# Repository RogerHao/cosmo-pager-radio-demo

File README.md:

# CosmoRadio

可穿梭于平行宇宙的 Radio 接收器

## 项目简介

桌面交互设备，安卓平板 + 3D 打印外壳 + ESP32 USB HID 控制器。造型参考 iMac G3 斜面站立式设计，用户通过旋钮调频、NFC 刷卡切换内容，仿佛在平行宇宙间搜索信号。

**当前版本：V4**（2026.04 — 2026.05）— 技术方案验证 + 单套原型制作

> 2026-04-29 与 Arthur 达成重启协议：第四期缩小为技术方案验证和单套原型制作，合同价 ¥5,000，目标 2026-05-20 左右交付。原 4 套整机 + 8 套电子套件交付范围已取消。

## 产品形态

- **外观风格**: iMac G3 斜面站立式，模块化三件式（主体 + 顶部 + 背板）
- **显示设计**: 三圆形遮罩（矩形屏幕通过开孔分割为三个圆形显示区）
- **输入方式**: 2 × EC11 旋钮 + Kailh 机械轴按钮 (6.25U 卫星轴) + NFC 刷卡
- **状态指示**: WS2812 RGB LED

## 硬件组成（V4）

| 组件 | 规格 | 用途 |
|------|------|------|
| 安卓平板 | 客户自购 (Samsung Galaxy Tab A9 8.7") | 主机，运行 Web 应用 |
| ESP32-S3 DevKitC N16R8 | 36+ GPIO / USB OTG / 16MB Flash / 8MB PSRAM | HID 控制器 |
| 定制 PCB 载板 | **100×100mm 双面** (JLCPCB 免费打样)，**两条 1×22 单排母** + 5 路 XH2.54 + 4× 10kΩ/10nF 去抖 | 消灭飞线，XH2.54 即插即用 |
| EC11 旋钮 × 2 | 15mm 半轴柄旋转编码器 | 频率调节 / 模式切换 |
| Kailh BOX 轴 + 6.25U 卫星轴 | 机械键盘蝴蝶结构，3.6mm 行程 | Action Button |
| RC522 mini NFC 模块 × 1 | 13.56MHz SPI，读 NTAG215 NDEF | NFC 刷卡交互（最终 1 个，2026-05-06 确认） |
| **OTG dongle (YK16-09E V1) 内置子板** | 拆 USB-A 母座，4 飞线接 J5 → DevKitC 排针 GPIO19/20 + 5V/GND | 平板 Data Host + Power Sink 同时工作 |
| 板载 RGB LED | DevKitC GPIO48 WS2812B | 状态指示（不外接 LED）|

## 连接方案

| 方案 | 固件位置 | 状态 |
|------|----------|------|
| USB HID | 项目根目录 | **当前使用** — TinyUSB，即插即用 |
| BLE HID | (已删除，见 git 历史) | V1-V2 遗留，已停用 |

## 交互设计

输入设备通过 ESP32 USB HID 协议作为标准键盘连接到安卓平板，事件以模拟按键传递：

| 输入 | 映射 | 功能 |
|------|------|------|
| 顶部 Action 按钮 | Enter 键 | 确认选择 |
| EC11 左 旋转 | 上/下方向键 | 调节频率 |
| EC11 左 按下 | F1（占位，平板可重映射） | 扩展功能位 |
| EC11 右 旋转 | 左/右方向键 | 切换模式 |
| EC11 右 按下 | F2（占位，平板可重映射） | 扩展功能位 |
| NFC 卡（写了 NDEF Text） | `<payload>\n` | **主路径**：固件读卡上写入的字符串，原样键入 + Enter（无前缀） |
| NFC 卡（空白 / 非 NDEF） | `NFC:<UID>\n` | 兜底：识别失败时键入 UID 方便诊断 |

### NFC 协议设计

为了让产品身份与 NFC 卡 UID 解耦（UID 不可控且需要逐张录入），固件读取卡上的 NDEF Text Record 内容作为产品 ID。流程：

1. 出厂前用任一手机 NFC 工具 app 把每张卡写入特定字符串（如 `R01`、`track-42`）
2. 用户放卡 → 固件读 NDEF → HID 键入 `R01\n`
3. 平板侧 Android 应用结合页面状态/输入长度判断当前是 NFC payload 还是普通 HID 键入；`NFC:` 前缀仅出现在 UID 兜底路径，方便区分

### LED 状态指示（DevKitC 板载 GPIO48 RGB LED）

| 事件 | LED 颜色 |
|------|----------|
| 按钮按下 | 红色 |
| 按钮释放 | 熄灭 |
| NFC 识别中（键入期间） | 蓝色 |
| 启动完成 | 绿色闪烁 |

## 项目结构

```
cosmo-radio/                            # 项目根 = ESP-IDF USB HID 固件
├── main/
│   ├── tusb_hid_example_main.c         # 入口：USB HID + ASCII→HID 编码
│   ├── input_handler.c/h               # GPIO 中断输入（按钮 + 双 EC11）
│   ├── nfc_handler.c/h                 # RC522 SPI 扫描 + NDEF Text 解析
│   └── led_indicator.c/h               # 板载 WS2812 RGB（GPIO48）
├── sdkconfig.defaults
├── CMakeLists.txt
├── pcb/                                # KiCad 工程 + JLCPCB 上板资料（待开始）
├── docs/
│   ├── assets/                         # 元器件引脚图、原型照片
│   ├── firmware/                       # 固件实现文档
│   ├── hardware/                       # 硬件模块设计方案（NFC、USB...）
│   ├── legacy/                         # 弃用内容
│   └── project/ → codex                # BOM、PCB Spec、项目主文档
└── test/
    └── hid-test.html
```

## 相关项目

- [cosmo-pager-web-nextjs-vercel](https://github.com/RogerHao/cosmo-pager-web-nextjs-vercel) — Web 应用前端（客户软件团队开发）

## 版本历史

| 版本 | 时间 | 主控 | 连接 | 主要变化 |
|------|------|------|------|----------|
| V1 | 2025 Q3-Q4 | Adafruit HUZZAH32 | — | 硬件预研 |
| V2 | 2025.12-2026.01 | XIAO ESP32S3 | BLE HID | 首批组装，硅谷交付 |
| V3 | 2026.01-2026.02 | ESP32-S3 SuperMini | USB HID | BLE→USB 切换，12 套交付 |
| **V4** | **2026.04-2026.05** | **ESP32-S3 DevKitC N16R8** | **USB HID** | **模块化 PCB + NFC + 机械按钮，单套原型验证** |

## V4 进度

**2026-05-07 整体技术方案验证完成 ✅**——电气、固件、NFC 协议端到端跑通。后续是 PCB 板设计 + 结构件设计。

电气与固件：
- [x] 原 12 套 BOM 定稿 + 报价（单套 ¥79，已取消）
- [x] 2026-04-29 与 Arthur 重启 V4：技术方案验证 + 单套原型，合同价 ¥5,000
- [x] USB-C 充电方案：被动 SS34 注入实测失败 → 改为内置一分二 OTG 线材小板（已采购验证）
- [x] NFC 数量确认：1 个 RC522 mini（2026-05-06）
- [x] 万能板飞线原型焊接 + GPIO 验证（2026-05-06，[图片](docs/assets/v4-handmade-prototype-2026-05-06.jpg)）
- [x] 固件 V4 GPIO 迁移（SuperMini → DevKitC N16R8）
- [x] NFC 驱动开发（RC522 SPI + NDEF Text Record 解析）
- [x] 旋钮 + NFC HID 协议定稿（`#<payload>\n` + UID 兜底）
- [x] 端到端验证：iPhone 写卡 → ESP32 读 NDEF → HID 键入 `#112358\n`（2026-05-07）

待办（V4 收尾）：
- [ ] PCB 载板设计（KiCad → JLCPCB），把万能板飞线版固化为正式板
- [ ] Arthur 寄新 Tab A9（原 Pad 已损坏）→ HID + 充电链路回归
- [ ] 按钮机构验证（6.25U 卫星轴空格键 + 3D 打印键帽）
- [ ] 外壳 3D 模型适配（Arthur Fusion 360）+ 打印装配
- [ ] 单套整机原型组装 + 整机测试
- [ ] 交付技术验证报告 + 单套原型

## 构建与烧录

```bash
get_idf                                    # 激活 ESP-IDF 环境
idf.py set-target esp32s3                  # 设置目标芯片（首次）
idf.py build                               # 构建
idf.py -p /dev/cu.usbmodem* flash monitor  # 烧录并监控
```

## GPIO 引脚分配（V4 终版）

> N16R8 = 8MB octal PSRAM，**GPIO 26-37 全段被内部 octal SPI flash + PSRAM 占用，不可使用**。完整表和"PCB 位置"列见 [CLAUDE.md](CLAUDE.md) "GPIO Pin Assignments"。

| 功能 | GPIO | 连接器 (PCB 位置) |
|------|------|--------|
| EC11-L (用户左旋钮) A/B/SW | **42 / 41 / 40** | J1 (PCB 左侧中段, 5P) |
| EC11-R (用户右旋钮) A/B/SW | **17 / 18 / 8** | J2 (PCB 右侧中段, 5P) |
| Action Button | 1 | J3 (PCB 左侧靠前, 2P) |
| RC522 NFC RST/IRQ/MISO/MOSI/SCK/CS | 4 / 5 / 6 / 7 / 15 / 16 | J4 (PCB 右侧, 8P, SPI2 via GPIO Matrix) |
| OTG USB D-/D+ | 19 / 20 | J5 (PCB 左侧靠后, 4P) → dongle USB |
| 板载 RGB LED | 48 | DevKitC 板载，无外接 LED |

> EC11 A/B 信号 PCB 上各加 10kΩ 上拉 + 10nF 对地 RC 去抖。
> V3 引脚分配（SuperMini）见 git 历史。

## 文档索引

- [V4 待办事项](TODO.md)
- [V4 BOM 及报价分析](docs/project/CosmoRadio-V4-BOM及报价分析.md)
- [V4 PCB 载板规格](docs/project/CosmoRadio-V4-PCB-Spec.md)
- [项目主文档](docs/project/cosmoradio-yangweile-customized-hardware.md)
- [USB 接口方案](docs/hardware/usb.md)
- [NFC 模块方案](docs/hardware/nfc.md)
- [OTG 一分二适配器（内置子板）](docs/hardware/otg-adapter.md)

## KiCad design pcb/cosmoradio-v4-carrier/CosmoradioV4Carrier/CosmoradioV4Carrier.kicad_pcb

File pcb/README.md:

# CosmoRadio V4 PCB

CosmoRadio V4 的 PCB 目标是做一块 ESP32-S3 DevKitC N16R8 载板，用于技术方案验证和单套原型制作。

当前阶段不追求量产最优，而是追求：

- 可快速打样
- 可手工装配
- 可稳定验证 USB HID、外部充电、旋钮、按钮、NFC
- 出问题时容易测量和返修

## 当前范围

| 项目 | 结论 |
|------|------|
| 合作状态 | 2026-04-29 与 Arthur 重启 V4 |
| 当前交付 | 技术方案验证 + 单套原型制作 |
| 合同价 | ¥5,000 |
| 目标时间 | 2026-05-20 左右 |
| 核心风险 | PCB 设计与验证 |
| 非当前目标 | 原 4 套整机 + 8 套电子件批量交付 |

## 2026-05-07 整体方案验证完成 ✅

| 项目 | 状态 |
|------|------|
| NFC 数量 | ✅ 确认 **1 个** RC522 mini |
| 一分二 OTG + 充电线材 | ✅ 已采购多种型号，测试出一种比较理想，作为内置子板基准 |
| 手工万能板原型 | ✅ 已焊出（[图片](../docs/assets/v4-handmade-prototype-2026-05-06.jpg)）：ESP32-S3 DevKitC + 拆解后的一分二小板 + 4 路 XH2.54 连接器 |
| 测试机 | ⚠️ 原 R4 Tab A9 已损坏，临时用安卓手机替代验证；新 Tab A9 到货后需回归 |
| 连接器布局 | 左上 J4 NFC 8P / 右上 J3 Action Button 2P / 左中 J1 EC11 左 5P / 右中 J2 EC11 右 5P |
| GPIO 分配 | ✅ V4 终版定稿（2026-05-06），详见 [CLAUDE.md](../CLAUDE.md) |
| 外接 LED | ❌ 不接（用 DevKitC 板载 GPIO48 RGB LED 做调试） |
| EC11 接线 | 3 IO + 共地（C 与 SW2 都接 GND，无需 VCC，靠 ESP32 内部上拉） |
| 固件 V4 GPIO 迁移 | ✅ 完成（2026-05-06）；V3 SuperMini pinout 完全弃用 |
| RC522 NFC 驱动 | ✅ 1MHz SPI，NDEF Text Record 解析跑通（2026-05-07） |
| HID 协议 | ✅ `#<payload>\n` 主路径 + `NFC:<UID>\n` 兜底（2026-05-07） |
| 端到端验证 | ✅ iPhone 写卡 "112358" → ESP32 读 NDEF → HID 键入 `#112358\n`（2026-05-07） |

**剩余工作集中在 PCB 设计 + 结构件**——所有方案级未知都已收敛。

## 下一阶段：PCB 落版（Plan v2，2026-05-18 锁定）

详细方案见 `~/.claude/plans/iridescent-snuggling-planet.md`。要点：

- 把万能板飞线版 1:1 复制到 KiCad（连接器位置、网络名都已经在飞线上验证过）
- ESP32-S3 DevKitC N16R8 用**两条 1×22 单排母**（不是 2×22 双排，单排好焊好对齐），间距 22.86mm
- **5 路 XH2.54 连接器**（J1 EC11-L / J2 EC11-R / J3 BTN / J4 NFC / J5 OTG USB 数据）
- OTG dongle (YK16-09E V1) 拆 USB-A 母座后 4 飞线焊到 J5 公头线
- **EC11 A/B 信号外加 10kΩ + 10nF RC 去抖**（4 R + 4 C，全 0805 贴片）—— 解决飞线版"一格不准"
- NFC SPI 时钟可尝试拉回 5MHz（铜箔走线 + 模块自带去耦应该够）
- 板尺寸 **100×100mm 双面板**（JLC 免费打样上限），无 USB-C 母座、无 SS34、无外接 LED

## 板子定位

这不是完整 ESP32 主控板，而是 **ESP32-S3 DevKitC N16R8 carrier board**。

ESP32-S3 DevKitC 通过 2.54mm 排母插在 PCB 上，PCB 只负责：

- 固定主控与外设线束
- 消灭 V3 的万能板和飞线
- 将旋钮、按钮、LED、NFC、USB-C 接口标准化
- 提供必要的上拉、电阻、二极管、去耦
- 支持单套原型的调试和返修

```mermaid
flowchart LR
    tablet[Android 平板] <-- USB HID --> pcb[CosmoRadio V4 PCB]
    charger[USB-C 充电器] --> pcb
    pcb --> devkit[ESP32-S3 DevKitC N16R8]
    pcb --> enc1[EC11 左旋钮]
    pcb --> enc2[EC11 右旋钮]
    pcb --> top[顶部按钮 / LED]
    pcb --> nfc[RC522 NFC 模块]
```

## 已确认事实

### 主控

- 使用 ESP32-S3 DevKitC N16R8，不再使用 V3 的 ESP32-S3 SuperMini。
- DevKitC 插在载板上，不直接焊死。
- ESP32-S3 原生 USB OTG 固定使用 GPIO19 / GPIO20。
- 当前固件仍是 V3/SuperMini pinout，后续必须迁移到 V4 pinout。

### 输入与输出

- 两个 EC11 旋钮，每个旋钮有 A / B / SW。
- Action Button 使用 Kailh BOX 轴 + 6.25U 卫星轴，本质是单路低电平按钮。
- LED 使用 WS2812B，数据线串 330R。
- NFC 使用 RC522 mini 模块，通过 SPI 连接，不把 MFRC522 芯片集成到主板。

### USB 与供电

- 平板是 Samsung Galaxy Tab A9 8.7"。
- 平板侧需要同时承担 USB Host 和充电需求。
- HID 必须走有线 USB；BLE HID 之前已经测试过，不稳定，排除出当前主路径。
- V3 已经通过 Type-C 一分二 OTG 线材验证：Tab A9/Android 手机可以同时接收 ESP32 USB HID 输入并充电。
- 当前问题不是“原理是否成立”，而是 V3 的一分二线材太长、外露、形态差。
- V4 目标是尽可能把一分二线材里的 OTG + 充电能力集成到 PCB/内部结构中，减少外露线材。
- 市面上容易买到的是 OTG + 充电转接线/小扩展坞，不是适合直接嵌入主 PCB 的裸模块。

```mermaid
flowchart LR
    tablet[Tab A9] <-- USB Host 数据 --> sub[内置一分二 OTG + 充电子系统]
    charger[USB-C 充电器] --> sub
    sub <-- USB HID --> esp[ESP32-S3 DevKitC]
    esp --> io[旋钮 / 按钮 / LED / NFC]
```

当前 USB/充电路径按三档处理：

| 档位 | 方案 | 当前定位 |
|------|------|----------|
| P0 | 外购一分二 OTG + 充电线材整件 | V3 已验证成立；继续作为功能基准 |
| P1 | 拆解一分二线材，取内部 PCB，短线/板内固定 | 当前最现实的 V4 原型方向 |
| P2 | 自研 LDR6028/LDR6023C OTG + 充电子板 | 可集成，但先作为后续方案，不塞进第一版主板风险内 |

被动 VBUS 注入方案已经降级为失败路径记录，不再作为主线：

- J6 充电输入 USB-C
- J5 平板输出 USB-C
- J6 VBUS 通过 SS34 注入 J5 VBUS
- J5 / J6 CC1 和 CC2 视转接板实测情况配置 5.1k Rd

原因：6P Type-C 转接板即使有 5.1k Rd，也只能让手机/平板识别到 OTG 设备；它不能让平板同时完成 Data Host 和 Power Sink 的角色组合。实测中，两个 6P 转接板直连、或通过 SS34 注入外部 5V，都无法让手机/平板进入充电状态。

不能把 CH224K、HUSB238 这类 PD Sink/诱骗芯片当成完整解法。它们主要解决“从充电器取电压”，不负责让平板同时保持数据 Host 和供电 Sink，也不负责完整 USB 数据/供电角色编排。

### USB/充电可选方案重审

问题本质：Tab A9 必须同时处于 **Data Host** 和 **Power Sink**。这不是普通 USB-C 默认角色，默认情况下 Host 往往也是供电 Source。要让平板一边 Host ESP32，一边被外部充电，需要角色拆分。

| 方案 | 是否能集成到主 PCB | 风险 | 结论 |
|------|-------------------|------|------|
| 拆解已验证一分二线材并内置小板 | 半集成 | 低中 | 第一版最现实，解决形态问题优先 |
| LDR6028 5V OTG + 充电子板 | 能 | 中 | 元件少，可后续小板验证；不一定比成品便宜 |
| LDR6023C 双口 charge-through 子板 | 能 | 中高 | 更接近成品线材内部方案，但外围更复杂 |
| 标准 USB-C PD charge-through | 能 | 高 | 正规方案，但不适合当前预算和周期 |
| 被动/半主动 SS34 注入 | 能 | 已实测失败 | 不再作为主线 |
| BLE HID + USB-C 只负责充电 | 能 | 低 | 已排除：BLE HID 实测不稳定，且当前要求必须有线 HID |

当前主路径：

1. 用已验证一分二线材作为功能基准。
2. 买 2-3 条同类线材拆解，优先寻找尺寸小、焊点清晰、可固定的内部 PCB。
3. 第一版 V4 主 PCB 给内置子板预留安装区、短线焊盘、测试点和应力释放。
4. 只有当成品线材内部 PCB 不适合内置，才启动 LDR6028/LDR6023C 自研小板。

标准 PD charge-through 架构如下：

```mermaid
flowchart LR
    charger[USB-C 充电器] --> sink[充电器侧 PD Sink 控制器]
    sink --> path[5V 电源路径 / eFuse / DC-DC]
    path --> tabletpd[平板侧 PD 控制器]
    tabletpd --> tablet[Tab A9: Power Sink + Data Host]
    tablet <-- USB2 D+/D- --> esp[ESP32-S3 USB HID Device]
```

这种方案需要：

- 平板侧 Type-C/PD 控制器：处理 Power Role Swap / Data Role Swap，使 Tab A9 保持 Host，同时从本设备受电。
- 充电器侧 PD Sink 控制器：从外部充电器取电。
- 电源路径保护：eFuse、限流、反灌保护、ESD、VBUS 放电。
- USB2 D+ / D- 路由：只有 ESP32 一个 USB 设备时不一定需要 USB Hub；若未来还有多个 USB 设备，才需要 Hub。
- PD 控制器配置或固件：这是主要工程风险。

已验证的一分二线材架构如下：

```mermaid
flowchart LR
    tablet[Tab A9 / Android 手机] <-- USB2 HID --> cable[一分二 OTG + 充电线材内部 PCB]
    charger[USB-C 充电器] --> cable
    cable <-- USB2 --> esp[ESP32-S3 HID]
```

它证明 Tab A9/Android 手机支持“Data Host + Power Sink”这个工作状态。失败的是我们用 6P 转接板和 SS34 复刻这个能力的被动电路，不是设备能力。

LDR6028 自研小板判断：

| 项目 | 判断 |
|------|------|
| 功能定位 | 5V OTG + 充电角色控制小板 |
| 预计新增元件 | 不含连接器约 16-22 个；含连接器约 18-24 个 |
| 单板元件成本 | 约 ¥15-20，不含 PCB、SMT、运费、返工 |
| 优点 | 形态可控，可最终集成 |
| 缺点 | 不比 20 元级成品线材便宜，且有兼容性调试风险 |

结论：LDR6028 的价值不是降成本，而是解决线材形态和长期可控性。对单套 V4 原型，优先拆解成品线材更理性。

已排除方案：BLE HID + USB-C 只负责充电：

```mermaid
flowchart LR
    charger[USB-C 充电器] --> pcb[主 PCB 电源输入]
    pcb --> tablet[短线给 Tab A9 充电]
    esp[ESP32-S3] <-- BLE HID --> tablet
    esp --> io[旋钮 / 按钮 / LED / NFC]
```

这个方案硬件上最容易集成到主 PCB：USB-C 只做供电，输入端可以用 PD Sink/诱骗芯片，输出端按 Type-C Source 给平板 5V。数据改为 BLE HID。但它违反当前硬约束，且 BLE HID 已实测不稳定，因此不作为 V4 路线。

### 有线 HID 下的当前建议

先做 **一分二线材拆解内置方案**，不要直接把 LDR6028/LDR6023C 或标准 PD charge-through 塞进第一版主 PCB。

2026-04-30 Manus 调研结论见 [Tab_A9_OTG_Charging_Feasibility_Report.md](research/Tab_A9_OTG_Charging_Feasibility_Report.md)。该报告针对“Tab A9 专用半主动方案”给出偏负面判断；后续实测一分二线材证明设备支持 HID + 充电，但也证明 6P 转接板 + SS34 这类被动复刻不够。

当前根据实测修正：

- 一分二 OTG + 充电线材已经证明 Tab A9/Android 手机可以同时 HID 输入和充电。
- 6P 转接板 + SS34 的失败说明不能靠简单 VBUS 注入和 CC 下拉复刻该线材。
- 第一版目标应先消灭外部长线，而不是立刻自研 USB-C 协议子系统。
- 标准 PD charge-through 仍是正规方向，但需要 PD 控制器配置、PD 协议调试、电源路径保护和可能的协议分析仪。
- V4 当前是技术验证 + 单套原型，合同价 ¥5,000，不能把主要预算压在 USB-C PD 协议栈调试上。

一分二线材拆解内置方案必须验证：

| 验证项 | 通过标准 |
|--------|----------|
| HID 枚举 | Tab A9 能识别 ESP32-S3 TinyUSB HID |
| 充电接入 | 插入外部充电器后 HID 不断连，系统显示充电 |
| 电池状态 | Android 显示充电，且电量能净增加 |
| 结构集成 | 拆解后的内部 PCB 能固定在外壳内，线长可缩短 |
| 热稳定 | 连续运行 2 小时无明显温升 |
| 恢复能力 | 平板重启、熄屏、亮屏、重插后能恢复 |

被动 SS34 注入实验记录如下，仅保留为排错依据。

最小验证拓扑只需要 1 颗 SS34：

```mermaid
flowchart LR
    chg[外部 5V] --> d1[SS34]
    d1 --> tabv[Tab A9 VBUS / SYS_5V]
    tabv --> esp[ESP32 5V]
    tab[Tab A9 D+/D-] <-- USB2 --> esp
```

这个拓扑里 `Tab_A9_VBUS` 和 `SYS_5V` 是同一个节点。不插外部电源时，平板作为 USB Host 给 ESP32 供电；插外部电源时，外部 5V 通过 SS34 尝试注入同一节点。SS34 的作用是防止平板 VBUS 反灌到外部充电器输入。

实测结果：6P 转接板能实现 USB HID，但不能实现充电。即使不接 ESP32，只把手机/平板和充电器通过两个 6P 转接板四线直连，也无法充电。原因是该电路没有完成 Type-C/PD 角色协商，平板不会因为 VBUS 被外部注入就切换到可充电状态。

更完整的诊断拓扑曾考虑 `SYS_5V` 电源 OR-ing，需要 3 颗 SS34：

```mermaid
flowchart LR
    tabv[Tab A9 VBUS] --> dt[隔离二极管 / 理想二极管]
    chg[外部 5V] --> dc[隔离二极管 / 理想二极管]
    dt --> sys[SYS_5V]
    dc --> sys
    sys --> esp[ESP32 5V]
    chg --> inj[肖特基 / 限流 / eFuse]
    inj --> tabv
    tab[Tab A9 D+/D-] <-- USB2 --> esp
```

原因：不插外部电源时，平板作为 USB Host 必须能从 `Tab_A9_VBUS` 给 ESP32 供电。若 ESP32 只接外部 `VBUS_IN`，则无法验证正常 OTG 使用场景。外部电源接入后，`VBUS_IN` 同时给 ESP32 供电，并通过隔离/限流路径尝试注入 `Tab_A9_VBUS` 给平板充电。

SS34 接线方向：电流从无色端流向有色条纹端，条纹端是阴极。`外部 5V -> Tab_A9_VBUS` 时，条纹端朝 `Tab_A9_VBUS`。

## 关键设计判断

### 采用混合焊接方案

第一版不做全直插件，也不做全贴片。

| 类型 | 方案 | 理由 |
|------|------|------|
| 电阻 | 0805 SMD | 适合加热台，易夹取，易返修 |
| 电容 | 0805 SMD | 适合加热台，布线短 |
| SS34 | SMA / DO-214AC SMD | 电流能力够，焊盘大，可返修 |
| JST-XH 连接器 | 直插件 | 插拔受力大，原型更可靠 |
| DevKitC 排母 | 直插件 | 承重和插拔受力，不适合贴片 |
| USB-C | DIP 转接板 / 2.54mm 排孔 | 第一版避免裸 USB-C SMT 焊接风险 |

判断：**低风险小器件贴片，高机械应力器件直插件**。这比全直插件更整洁，也比全贴片更适合单套原型。

### 不把 USB-C 母座直接做成 SMT 主件

裸 USB-C SMT 母座对第一版不划算：

- 焊盘密，短路排查成本高
- 插拔受力大，需要外壳和板边机械支撑
- 3D 模型和 footprint 容易踩坑
- D+ / D- / CC 任何问题都会让 USB 调试变复杂

第一版主板使用已有 6P USB-C DIP 转接板更稳。OTG + 充电子系统如果采用拆板方案，则作为独立子板固定，不把未知小板强行复刻进主 PCB。

### 先解决线材形态，不先挑战 USB-C 协议

当前真正问题不是“有没有转接器”，而是“转接器线太长、外露、丑”。因此第一轮验证目标应改成：

1. 买 2-3 个便宜 OTG + 充电转接器。
2. 逐个做 Tab A9 + ESP32-S3 HID + 充电稳定性复测。
3. 拆开最稳定、体积最小的一款，记录内部 PCB 尺寸、接口、焊点、芯片丝印。
4. 将其作为内置子板固定在外壳内，用短线或板内焊点连接主板。
5. 主 PCB 只为它预留 USB HID 接口、5V/GND 测试点、安装空间和应力释放结构。

这个路线比从零设计 USB-C PD/OTG 子板更快，也比把完整转接线塞进外壳更干净。

### NFC 连接器按 8P 处理

文档里曾出现 7P / 8P 不一致。以 RC522 mini 实物和 NFC 文档为准，采用 8P：

| Pin | RC522 丝印 | 信号 |
|-----|------------|------|
| 1 | SDA | CS |
| 2 | SCK | SCK |
| 3 | MOSI | MOSI |
| 4 | MISO | MISO |
| 5 | IRQ | IRQ |
| 6 | GND | GND |
| 7 | RET | RST |
| 8 | 3V3 | 3V3 |

IRQ 可选，但第一版建议接出，避免后续想做中断驱动时改板。

### 顶部按钮和 LED 暂时分开连接

PCB Spec 曾建议将按钮和 LED 合并为 4P 顶部模块连接器。BOM 里按钮和 LED 是分开的 2P + 3P。

第一版建议分开：

- BTN：2P XH2.54
- LED：3P XH2.54

理由：

- 原型更容易测试
- 按钮和 LED 可独立替换
- 顶部模块结构未最终定型，分开线束更灵活

## 接口定义（Plan v2，最终版）

权威 GPIO 表见 [CLAUDE.md](../CLAUDE.md) "GPIO Pin Assignments"。下表为 PCB 视角连接器列表：

| Ref | 接口 | 类型 | 连接对象 | 信号（按 pin 顺序）|
|-----|------|------|----------|------|
| U1A | DevKitC 左列 socket | 1×22P 排母 2.54mm | ESP32-S3 DevKitC N16R8 左侧排针 | 22 pin，含 19/20/21/35-44/1/2/5V/GND |
| U1B | DevKitC 右列 socket | 1×22P 排母 2.54mm | ESP32-S3 DevKitC N16R8 右侧排针 | 22 pin，含 3V3/RST/4-18/3/46/9-14 |
| J1 | EC11-L (用户左旋钮) | XH2.54 5P | 左旋钮 | A=42, B=41, SW=40, GND, GND |
| J2 | EC11-R (用户右旋钮) | XH2.54 5P | 右旋钮 | A=17, B=18, SW=8, GND, GND |
| J3 | BTN | XH2.54 2P | Kailh BOX 按钮 | SIG=1, GND |
| J4 | NFC | XH2.54 8P | RC522 mini | CS=16, SCK=15, MOSI=7, MISO=6, IRQ=5, GND, RST=4, 3V3 |
| J5 | OTG USB 数据 | XH2.54 4P | OTG dongle (YK16-09E V1) 拆 USB-A 后 4 飞线 | VBUS, D-=19, D+=20, GND |

> **U1A 中心距 U1B = 22.86mm** (= 9 × 2.54mm pitch)，breadboard 兼容。以飞线万能板实测为准。

## 原理图元件清单（Plan v2，14 元件）

| Ref | 元件 | 封装 | 说明 |
|-----|------|------|------|
| U1A, U1B | 1×22P 排母座 (×2) | 2.54mm THT | DevKitC 插入用 |
| J1, J2 | XH2.54 5P 立式直针座 (×2) | THT | EC11 旋钮 |
| J3 | XH2.54 2P 立式直针座 | THT | Action Button |
| J4 | XH2.54 8P 立式直针座 | THT | RC522 NFC |
| J5 | XH2.54 4P 立式直针座 | THT | OTG dongle USB 数据 |
| R1, R2 | 10kΩ 上拉 (EC11-L A/B) | 0805 | LCSC C17414 |
| R3, R4 | 10kΩ 上拉 (EC11-R A/B) | 0805 | LCSC C17414 |
| C1, C2 | 10nF 对 GND (EC11-L A/B) | 0805 X7R 50V | RC 去抖，τ=100µs |
| C3, C4 | 10nF 对 GND (EC11-R A/B) | 0805 X7R 50V | 同上 |
| H1-H4 | M2.5 安装孔 | 通孔 | 四角 |

**取消的元件**（vs 旧 spec）：USB-C 母座 J5/J6、USB-C CC 5.1k Rd × 4、SS34 防倒灌、WS2812B LED 连接器 J4 (旧)、330Ω LED 限流。所有 USB 充电由 OTG dongle 内部承担，LED 用 DevKitC GPIO48 板载 RGB。

## PCB 物理约束

| 项目 | 目标 |
|------|------|
| 尺寸 | **100mm × 100mm**（JLC 免费打样上限）|
| 层数 | 2 层 |
| 板厚 | 1.6mm |
| 铜厚 | 1oz |
| 表面 | HASL 无铅 |
| 阻焊 | 黑色 |
| 丝印 | 白色 |
| 安装孔 | 4 × M2.5（四角，孔径 2.7mm）|
| 制造 | JLCPCB 5 片打样 |
| SMT 装配 | 不上 SMT；纯打板，8 个 0805 + 6 个连接器手焊 ~15min |

## 布局原则（Plan v2）

- DevKitC 居中，USB-C OTG 端朝外壳后侧（用户视角顶部）
- 连接器位置就近其需要的 GPIO（最短走线）：
  - **PCB 左侧**：J5 USB (靠后, GPIO 19/20) / J1 EC11-L (中段, GPIO 42/41/40) / J3 BTN (靠前, GPIO 1)
  - **PCB 右侧**：J4 NFC (中段, GPIO 4-7/15-16) / J2 EC11-R (中段偏上, GPIO 17/18/8)
- R/C 去抖网络紧贴 J1/J2 的 A/B pin（电容回 GND 路径最短）
- VBUS 走线宽度 ≥ 0.6mm（dongle 充电电流过路）
- USB D+/D- 短、并行、少过孔（<10cm 距离，无需阻抗控制）
- 每个连接器旁边丝印接口名 + pin 功能（≥1.0mm 高，gotcha #6）
- 顶丝印加 **"OTG USB-C: DO NOT PLUG"** 警示

## 已关闭的问题（Plan v2 收敛）

| 旧问题 | 决议 |
|--------|------|
| DevKitC N16R8 实物 pinout 和排母间距 | 22.86mm，参 `pcb/asset/ESP32-S3-DevKitC-N16R8.png` |
| USB-C DIP 转接板尺寸 | 不用——OTG dongle 替代 |
| OTG + 充电转接器选型 + 拆解 | YK16-09E V1，已确定 |
| NFC 数量 | 1 个 RC522 mini，已锁 |
| 顶部模块线束 BTN+LED 合并？| 分开——BTN 2P (J3)，不外接 LED |
| 80×50 是否够 | 改 100×100 直接给到 JLC 免费打样上限 |
| 第二版扩展接口 | 不预留，U1A/U1B 自然暴露所有未用 GPIO |

## 下一步

1. ✅ ~~实测 DevKitC 排针尺寸~~ — 22.86mm 已确认
2. ✅ ~~拆 OTG dongle 选型~~ — YK16-09E V1 已用于飞线版
3. ⏳ KiCad 原理图（circuit-synth Phase 2）
4. ⏳ 生成 100×100mm PCB layout（Phase 4）
5. ⏳ Freerouting + DRC 0/0（Phase 5）
6. ⏳ 出 Gerber zip 上传 JLCPCB（Phase 7）

执行节奏见 `~/.claude/plans/iridescent-snuggling-planet.md`。

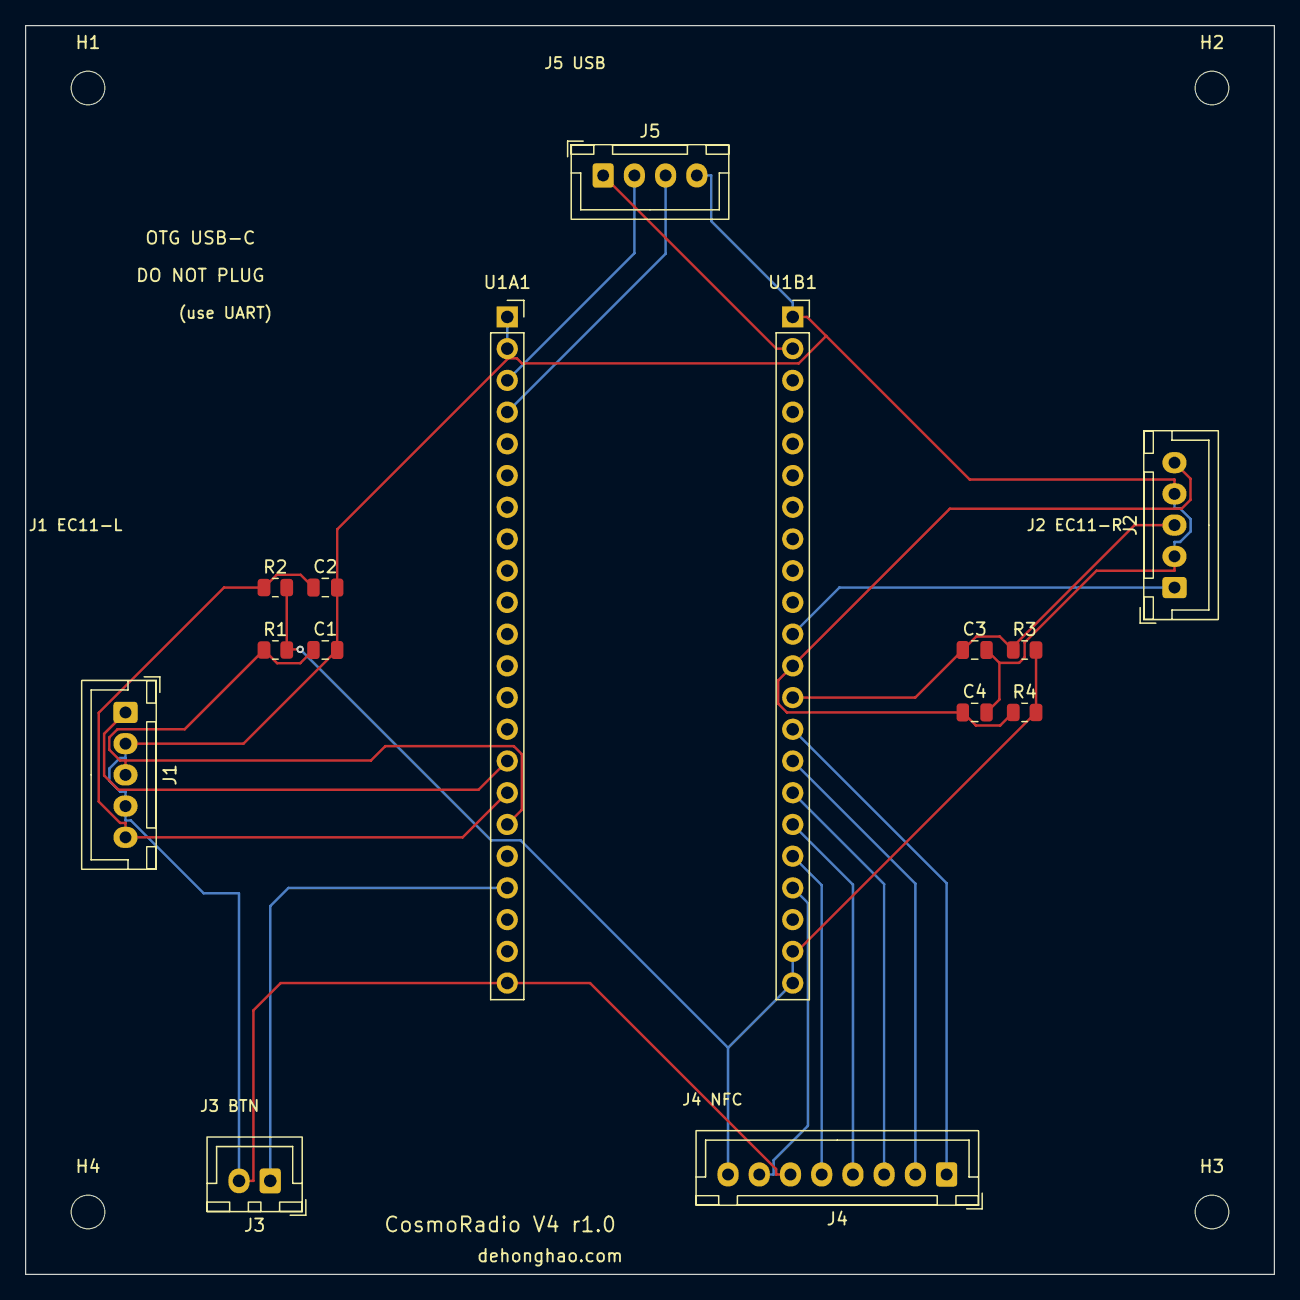
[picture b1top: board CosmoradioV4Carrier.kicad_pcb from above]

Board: 2 copper layers, 100.0 x 100.0 mm, 19 parts (0 on the bottom side), 18 nets.

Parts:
C1, C2, C3, C4: 10nF; C_0805_2012Metric
H1, H2, H3, H4: MountingHole_2.7mm_M2.5
J1: EC11-L; JST_XH_B5B-XH-A_1x05_P2.50mm_Vertical
J2: EC11-R; JST_XH_B5B-XH-A_1x05_P2.50mm_Vertical
J3: BTN; JST_XH_B2B-XH-A_1x02_P2.50mm_Vertical
J4: NFC; JST_XH_B8B-XH-A_1x08_P2.50mm_Vertical
J5: USB-DONGLE; JST_XH_B4B-XH-A_1x04_P2.50mm_Vertical
R1, R2, R3, R4: 10k; R_0805_2012Metric
U1A1: DevKitC-L; PinSocket_1x22_P2.54mm_Vertical
U1B1: DevKitC-R; PinSocket_1x22_P2.54mm_Vertical

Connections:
3V3: J4.8, R1.2, R2.2, R3.2, R4.2, U1B1.21, U1B1.22
5V: J5.1, U1B1.2
BTN: J3.1, U1A1.19
ENC1_A: C1.1, J1.3, R1.1, U1A1.17
ENC1_B: C2.1, J1.5, R2.1, U1A1.16
ENC1_SW: J1.1, U1A1.15
ENC2_A: C3.1, J2.3, R3.1, U1B1.13
ENC2_B: C4.1, J2.5, R4.1, U1B1.12
ENC2_SW: J2.1, U1B1.11
GND: C1.2, C2.2, C3.2, C4.2, J1.2, J1.4, J2.2, J2.4, J3.2, J4.6, J5.4, U1A1.1, U1A1.2, U1A1.22, U1B1.1
NFC_CS: J4.1, U1B1.14
NFC_IRQ: J4.5, U1B1.18
NFC_MISO: J4.4, U1B1.17
NFC_MOSI: J4.3, U1B1.16
NFC_RST: J4.7, U1B1.19
NFC_SCK: J4.2, U1B1.15
USB_DM: J5.2, U1A1.3
USB_DP: J5.3, U1A1.4

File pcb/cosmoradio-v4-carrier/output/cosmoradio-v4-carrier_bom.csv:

"Refs","Value","Footprint","Qty","DNP"
"C1","10nF","Capacitor_SMD:C_0805_2012Metric","1",""
"C2","10nF","Capacitor_SMD:C_0805_2012Metric","1",""
"C3","10nF","Capacitor_SMD:C_0805_2012Metric","1",""
"C4","10nF","Capacitor_SMD:C_0805_2012Metric","1",""
"J1","EC11-L-5P","Connector_JST:JST_XH_B5B-XH-A_1x05_P2.50mm_Vertical","1",""
"J2","EC11-R-5P","Connector_JST:JST_XH_B5B-XH-A_1x05_P2.50mm_Vertical","1",""
"J3","BTN-2P","Connector_JST:JST_XH_B2B-XH-A_1x02_P2.50mm_Vertical","1",""
"J4","NFC-8P","Connector_JST:JST_XH_B8B-XH-A_1x08_P2.50mm_Vertical","1",""
"J5","USB-DONGLE-4P","Connector_JST:JST_XH_B4B-XH-A_1x04_P2.50mm_Vertical","1",""
"R1","10k","Resistor_SMD:R_0805_2012Metric","1",""
"R2","10k","Resistor_SMD:R_0805_2012Metric","1",""
"R3","10k","Resistor_SMD:R_0805_2012Metric","1",""
"R4","10k","Resistor_SMD:R_0805_2012Metric","1",""
"U1A1","DevKitC-Left-Socket","Connector_PinSocket_2.54mm:PinSocket_1x22_P2.54mm_Vertical","1",""
"U1B1","DevKitC-Right-Socket","Connector_PinSocket_2.54mm:PinSocket_1x22_P2.54mm_Vertical","1",""

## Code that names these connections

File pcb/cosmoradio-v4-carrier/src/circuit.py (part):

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    #  3=GPIO19(USB D-), 4=GPIO20(USB D+), 5=GPIO21, 6=GPIO47,
    #  7=GPIO48, 8=GPIO45, 9=GPIO0, 10=GPIO35, 11=GPIO36, 12=GPIO37,
    #  13=GPIO38, 14=GPIO39, 15=GPIO40(ENC1 SW), 16=GPIO41(ENC1 B),
    #  17=GPIO42(ENC1 A), 18=GPIO2, 19=GPIO1(BTN), 20=GPIO44(RX0),
    #  21=GPIO43(TX0), 22=GND
    u1a = Component(
        symbol="Connector_Generic:Conn_01x22",
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    gnd = Net("GND")

    # EC11-L 信号 (用户左旋钮)
    enc1_a = Net("ENC1_A")    # GPIO42
    enc1_b = Net("ENC1_B")    # GPIO41
    enc1_sw = Net("ENC1_SW")  # GPIO40

    # EC11-R 信号 (用户右旋钮)
    enc2_a = Net("ENC2_A")    # GPIO17
    enc2_b = Net("ENC2_B")    # GPIO18
    enc2_sw = Net("ENC2_SW")  # GPIO8

    # Action Button
    btn = Net("BTN")          # GPIO1

    # NFC SPI + control
    nfc_cs = Net("NFC_CS")      # GPIO16
    nfc_sck = Net("NFC_SCK")    # GPIO15
    nfc_mosi = Net("NFC_MOSI")  # GPIO7
    nfc_miso = Net("NFC_MISO")  # GPIO6
    nfc_irq = Net("NFC_IRQ")    # GPIO5
    nfc_rst = Net("NFC_RST")    # GPIO4

    # USB OTG (走 J5 到 dongle)
    usb_dm = Net("USB_DM")    # GPIO19
    usb_dp = Net("USB_DP")    # GPIO20

    # ====================================================================
    # CONNECTIONS — U1A (DevKitC 左列插座)
    # ====================================================================
    u1a[1] += gnd         # GND (pin 1)
    u1a[2] += gnd         # GND (pin 2 — 不是 5V! 实测 user-LEFT 顶部连续两个 GND)
    u1a[3] += usb_dm      # GPIO19 (USB D-)
    u1a[4] += usb_dp      # GPIO20 (USB D+)
    # u1a[5-14]: GPIO 21/47/48/45/0/35-39 — 未使用,不接 net
    u1a[15] += enc1_sw    # GPIO40 (ENC1 SW)
    u1a[16] += enc1_b     # GPIO41 (ENC1 B)
    u1a[17] += enc1_a     # GPIO42 (ENC1 A)
    # u1a[18]: GPIO2 — 未使用
    u1a[19] += btn        # GPIO1 (BTN SIG)
    # u1a[20-21]: GPIO44/43 (UART0) — 不接,留给烧录调试
    u1a[22] += gnd        # GND

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    u1b[1] += gnd         # GND
    u1b[2] += p5v         # 5V — 主供电（U1A pin 2 是 GND，5V 只在这里）
    # u1b[3-10]: GPIO 14/13/12/11/10/9/46/3 — 未使用
    u1b[11] += enc2_sw    # GPIO8 (ENC2 SW)
    u1b[12] += enc2_b     # GPIO18 (ENC2 B)
    u1b[13] += enc2_a     # GPIO17 (ENC2 A)
    u1b[14] += nfc_cs     # GPIO16 (NFC CS)
    u1b[15] += nfc_sck    # GPIO15 (NFC SCK)
    u1b[16] += nfc_mosi   # GPIO7 (NFC MOSI)
    u1b[17] += nfc_miso   # GPIO6 (NFC MISO)
    u1b[18] += nfc_irq    # GPIO5 (NFC IRQ)
    u1b[19] += nfc_rst    # GPIO4 (NFC RST)
    # u1b[20]: RST (CHIP_PU/EN) — 不接,DevKitC 自有 RST 按钮
    u1b[21] += p3v3       # 3V3
    u1b[22] += p3v3       # 3V3 (双 3V3 pin 并联,降阻)
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    # ====================================================================
    # CONNECTIONS — J3 (Action Button 2P)
    # ====================================================================
    j3[1] += btn          # SIG (GPIO1)
    j3[2] += gnd          # GND

    # ====================================================================
    # CONNECTIONS — J4 (NFC 8P, 顺序与 RC522 mini 模块 1:1)
    # ====================================================================
    j4[1] += nfc_cs       # CS  (GPIO16)
    j4[2] += nfc_sck      # SCK (GPIO15)
    j4[3] += nfc_mosi     # MOSI(GPIO7)
    j4[4] += nfc_miso     # MISO(GPIO6)
    j4[5] += nfc_irq      # IRQ (GPIO5, 固件未用但接线预留)
    j4[6] += gnd          # GND
    j4[7] += nfc_rst      # RST (GPIO4)
    j4[8] += p3v3         # 3V3

    # ====================================================================
    # CONNECTIONS — J5 (OTG dongle USB 数据 4P, 与 USB-A 物理顺序一致)
    # ====================================================================
    j5[1] += p5v          # VBUS
    j5[2] += usb_dm       # D- (GPIO19)
    j5[3] += usb_dp       # D+ (GPIO20)
    j5[4] += gnd          # GND


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
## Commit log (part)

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2026-04-30 chore: pcb — scaffold board workspace
2026-04-30 docs: pcb — record USB charge strategy
2026-04-30 docs: pcb — fix OTG validation power path
